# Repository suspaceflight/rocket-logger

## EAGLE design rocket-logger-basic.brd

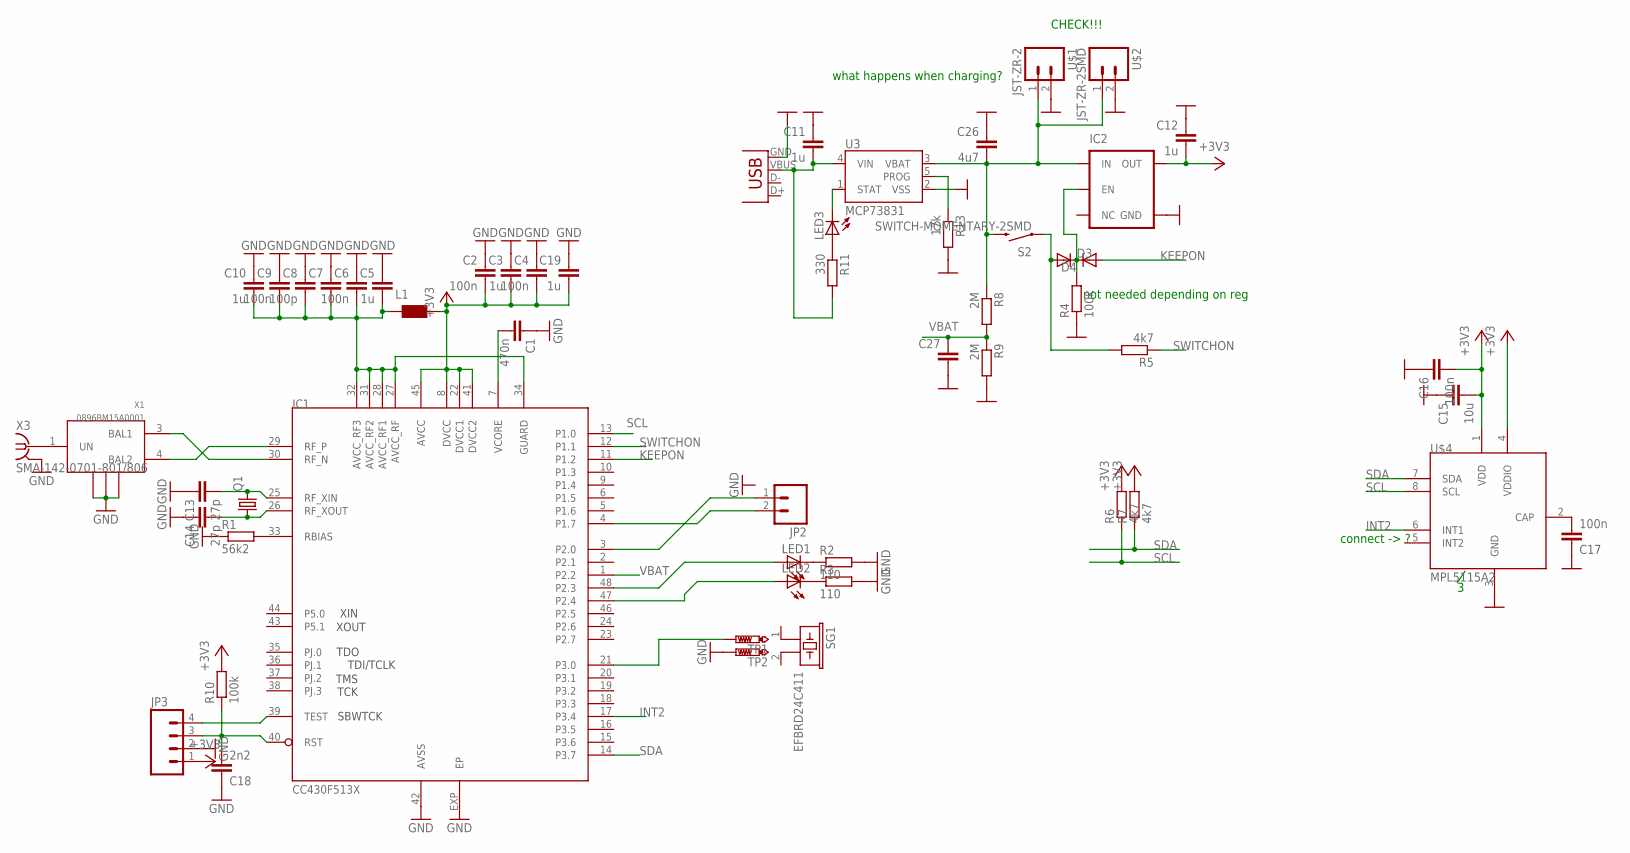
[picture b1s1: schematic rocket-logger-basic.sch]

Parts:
C1: 470n; C0402
C2, C4, C6, C9, C16, C17: 100n; C0402
C3, C5, C10, C11, C12, C19: 1u; C0402
C7, C27: C-EUC0402; C0402
C8: 100p; C0402
C13, C14: 27p; C0402
C15: 10u; C0402
C18: 2n2; C0402
C26: 4u7; C0402
D3, D4: DIODE-SOD523; SOD523
IC1: CC430F513X; QFN48
IC2: V_REG_TPS76433SOT23-5; SOT23-5
JP2: M02PTH; 1X02
JP3: M04PTH; 1X04
L1: WE-MK_0603; 0603
LED1, LED2, LED3: LED0603; LED-0603
Q1: CRYSTAL5X3; CRYSTAL-SMD-5X3
R1: 56k2; R0402
R2, R3: 110; R0402
R4, R10: 100k; R0402
R5, R6, R7: 4k7; R0402
R8, R9: 2M; R0402
R11: 330; R0402
R13: 17k; R0402
S2: SWITCH-MOMENTARY-2SMD; TACTILE_SWITCH_SMD
SG1: EFBRD24C411
TP1, TP2: PTR1B1,27; B1,27
U3: MCP73831; SOT23-5
U$1: JST-ZR-2
U$2: JST-ZR-2SMD; JST-ZR-2-SMD
U$4: MPL5115A2; LGA8
X1: 0896BM15A0001
X2: USB-MICROB
X3: SMA-142-0701-801/806; J502-ND-142-0701-801/806

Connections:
+3V3: C2.2, C3.2, C4.2, C12.2, C15.2, C16.2, C19.2, IC1.8 (DVCC), IC1.22 (DVCC1), IC1.41 (DVCC2), IC1.45 (AVCC), IC2.5 (OUT), JP3.1, L1.2, R6.2, R7.2, R10.2, U$4.1 (VDD), U$4.4 (VDDIO)
AVCC_RF2: C5.2, C6.2, C7.2, C8.2, C9.2, C10.2, IC1.27 (AVCC_RF), IC1.28 (AVCC_RF1), IC1.31 (AVCC_RF2), IC1.32 (AVCC_RF3), IC1.34 (GUARD), L1.1
GND: C1.1, C2.1, C3.1, C4.1, C5.1, C6.1, C7.1, C8.1, C9.1, C10.1, C11.1, C12.1, C13.1, C14.1, C15.1, C16.1, C17.1, C18.1, C19.1, C26.1, C27.2, IC1.42 (AVSS), IC1.EXP (EP), IC2.2 (GND), JP3.2, R1.1, R2.2, R3.2, R4.1, R9.2, R13.2, TP2.TP, U3.2 (VSS), U$1.2, U$2.2, U$4.3 (GND), X1.2 (GND2), X1.5 (GND), X1.6 (GND1), X2.GND, X3.G@1 (GND), X3.G@2 (GND), X3.G@3 (GND), X3.G@4 (GND)
INT2: IC1.17 (P3.4), U$4.6 (INT1)
KEEPON: D4.A, IC1.11 (P1.2)
unnamed: R13.1, U3.5 (PROG)
unnamed: C26.2, IC2.1 (IN), R8.1, S2.3 (2), U3.3 (VBAT), U$1.1, U$2.1
unnamed: IC1.30 (RF_N), X1.3 (BAL1)
unnamed: IC1.29 (RF_P), X1.4 (BAL2)
unnamed: IC1.33 (RBIAS), R1.2
unnamed: C13.2, IC1.25 (RF_XIN), Q1.3 (2)
unnamed: C14.2, IC1.26 (RF_XOUT), Q1.1
unnamed: X1.1 (UN), X3.1
unnamed: LED1.C, R2.1
unnamed: LED2.C, R3.1
unnamed: IC1.3 (P2.0), JP2.1
unnamed: IC1.4 (P1.7), JP2.2
unnamed: C17.2, U$4.2 (CAP)
unnamed: LED3.A, R11.1
unnamed: IC1.48 (P2.3), LED1.A
unnamed: C11.2, R11.2, U3.4 (VIN), X2.VBUS
unnamed: LED3.C, U3.1 (STAT)
unnamed: IC1.39 (TEST), JP3.4
unnamed: D3.A, R5.2, S2.1
unnamed: D3.C, D4.C, IC2.3 (EN), R4.2
unnamed: C18.2, IC1.40 (RST), JP3.3, R10.1
unnamed: IC1.47 (P2.4), LED2.A
unnamed: IC1.21 (P3.0), TP1.TP
SCL: IC1.13 (P1.0), R6.1, U$4.8 (SCL)
SDA: IC1.14 (P3.7), R7.1, U$4.7 (SDA)
SWITCHON: IC1.12 (P1.1), R5.1
VBAT: C27.1, IC1.1 (P2.2), R8.2, R9.1
VCORE: C1.2, IC1.7 (VCORE)

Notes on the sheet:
CHECK!!!
connect -> ?
what happens when charging?
not needed depending on reg

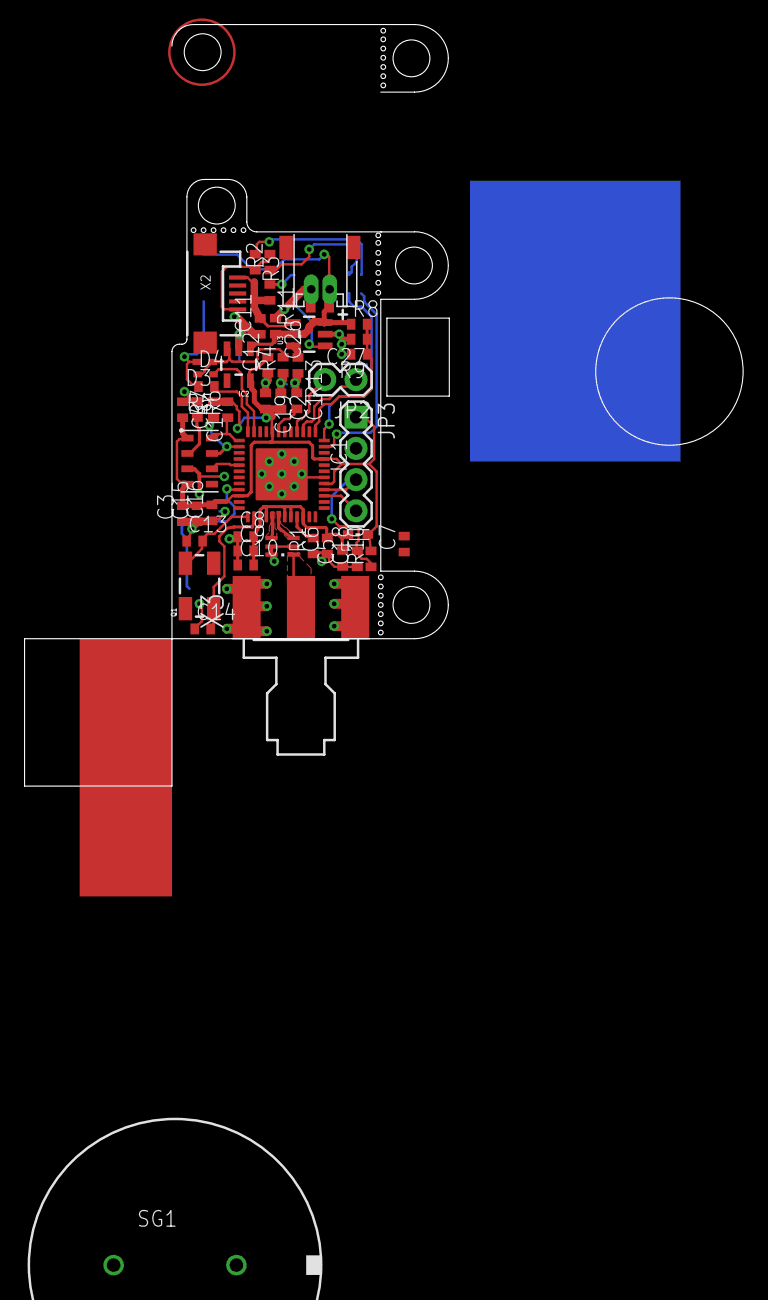
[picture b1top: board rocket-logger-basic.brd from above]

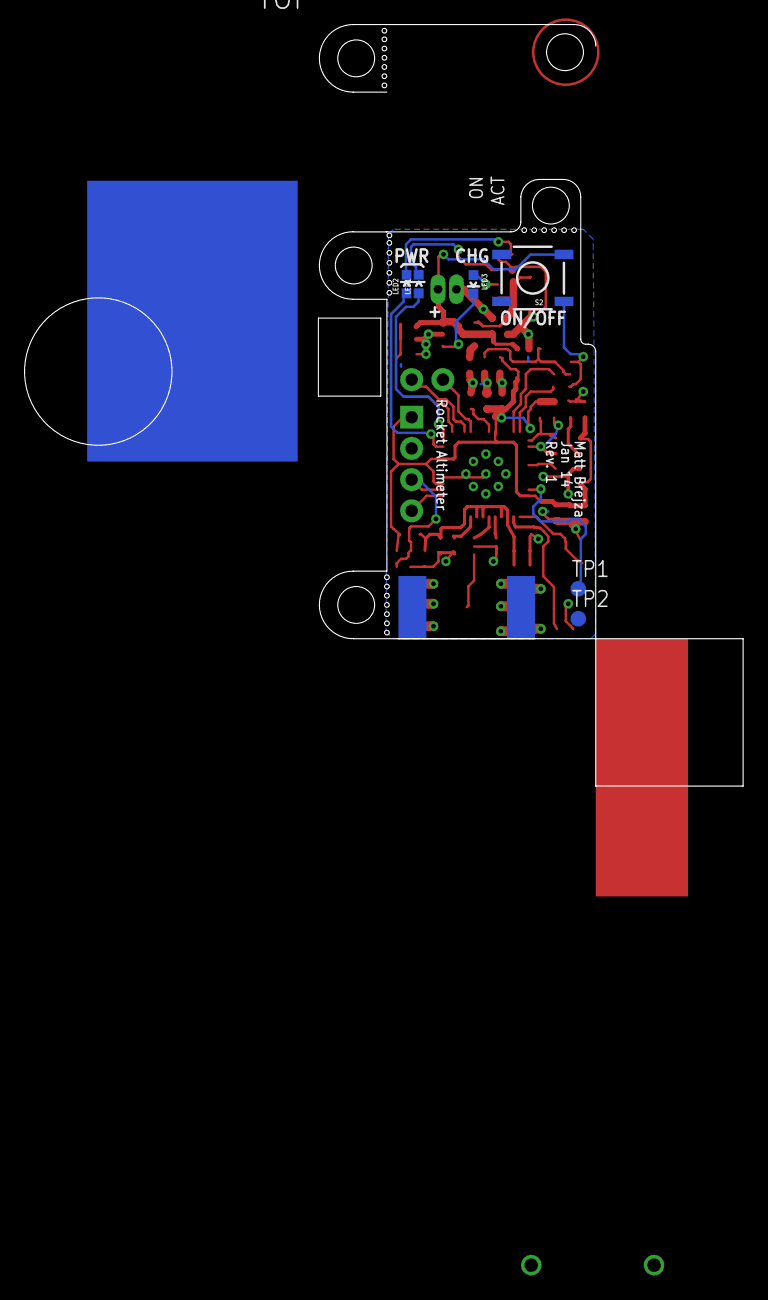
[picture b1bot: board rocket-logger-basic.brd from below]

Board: 2 copper layers, 34.5 x 49.4 mm, 55 parts (6 on the bottom side), 33 nets.

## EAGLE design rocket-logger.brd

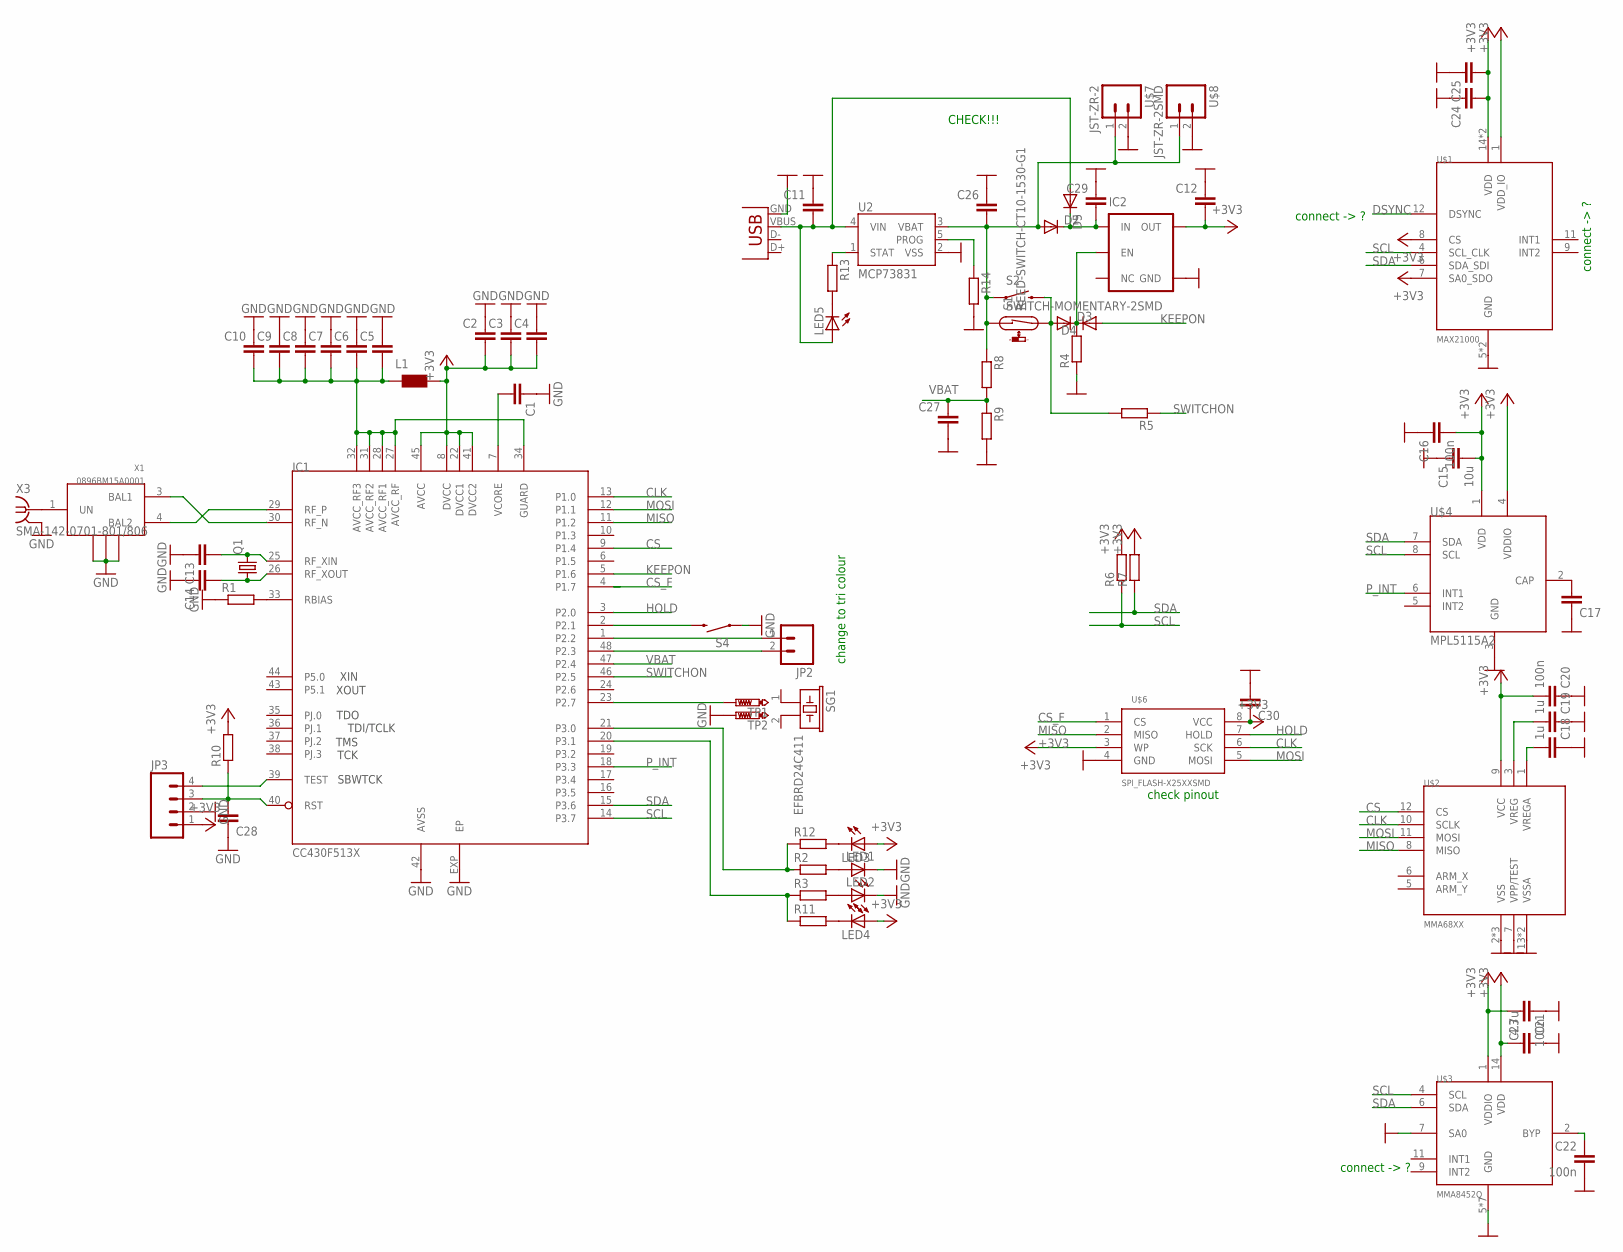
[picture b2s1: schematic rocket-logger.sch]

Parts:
C1, C2, C3, C4, C5, C6, C7, C8, C9, C10, C11, C12, C13, C14, C17, C24, C25, C26, C27, C28, C29, C30: C-EUC0402; C0402
C15: 10u; C0402
C16, C20, C22, C23: 100n; C0402
C18, C19: 1u; C0402
C21: 4.7u; C0402
D2, D3, D4, D5: DIODE-SOD523; SOD523
IC1: CC430F513X; QFN48
IC2: V_REG_TPS76433SOT23-5; SOT23-5
JP2: M02PTH; 1X02
JP3: M04PTH; 1X04
L1: WE-MK_0603; 0603
LED1, LED2, LED3, LED4, LED5: LED0603; LED-0603
Q1: CRYSTAL5X3; CRYSTAL-SMD-5X3
R1, R2, R3, R4, R5, R6, R7, R8, R9, R10, R11, R12, R13, R14: R-EU_R0402; R0402
S1: REED-SWITCH-CT10-1530-G1; CT10-G1
S2, S4: SWITCH-MOMENTARY-2SMD; TACTILE_SWITCH_SMD
SG1: EFBRD24C411
TP1, TP2: PTR1B1,27; B1,27
U2: MCP73831; SOT23-5
U$1: MAX21000; LGA16
U$2: MMA68XX; QFN16-6X6
U$3: MMA8452Q; QFN16-COL
U$4: MPL5115A2; LGA8
U$6: SPI_FLASH-X25XXSMD; SO08
U$7: JST-ZR-2
U$8: JST-ZR-2SMD; JST-ZR-2-SMD
X1: 0896BM15A0001
X2: USB-MICROB
X3: SMA-142-0701-801/806; J502-ND-142-0701-801/806

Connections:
+3V3: C2.2, C3.2, C4.2, C12.2, C15.2, C16.2, C20.2, C21.2, C23.1, C24.2, C25.2, C30.1, IC1.8 (DVCC), IC1.22 (DVCC1), IC1.41 (DVCC2), IC1.45 (AVCC), IC2.5 (OUT), JP3.1, L1.2, LED3.A, LED4.A, R6.2, R7.2, R10.2, U$1.1 (VDD_IO), U$1.7 (SA0_SDO), U$1.8 (CS), U$1.14 (VDD), U$1.15 (VDD), U$2.9 (VCC), U$3.1 (VDDIO), U$3.14 (VDD), U$4.1 (VDD), U$4.4 (VDDIO), U$6.3 (WP), U$6.8 (VCC)
AVCC_RF2: C5.2, C6.2, C7.2, C8.2, C9.2, C10.2, IC1.27 (AVCC_RF), IC1.28 (AVCC_RF1), IC1.31 (AVCC_RF2), IC1.32 (AVCC_RF3), IC1.34 (GUARD), L1.1
CLK: IC1.13 (P1.0), U$2.10 (SCLK), U$6.6 (SCK)
CS: IC1.9 (P1.4), U$2.12 (CS)
CS_F: IC1.4 (P1.7), U$6.1 (CS)
DSYNC: U$1.12 (DSYNC)
GND: C1.1, C2.1, C3.1, C4.1, C5.1, C6.1, C7.1, C8.1, C9.1, C10.1, C11.1, C12.1, C13.1, C14.1, C15.1, C16.1, C17.1, C18.1, C19.1, C20.1, C21.1, C22.2, C23.2, C24.1, C25.1, C26.1, C27.2, C28.1, C29.1, C30.2, IC1.42 (AVSS), IC1.EXP (EP), IC2.2 (GND), JP3.2, LED1.C, LED2.C, R1.1, R4.1, R9.2, R14.2, S4.1, TP2.TP, U2.2 (VSS), U$1.5 (GND), U$1.10 (GND), U$2.2 (VSS), U$2.4 (VSS), U$2.7 (VPP/TEST), U$2.13 (VSSA), U$2.16 (VSSA), U$2.17 (VSS), U$3.5 (GND), U$3.7 (SA0), U$3.8 (GND), U$3.10 (GND), U$3.12 (GND), U$3.13 (GND), U$3.15 (GND), U$3.16 (GND), U$4.3 (GND), U$6.4 (GND), U$7.2, U$8.2, X1.2 (GND2), X1.5 (GND), X1.6 (GND1), X2.GND, X3.G@1 (GND), X3.G@2 (GND), X3.G@3 (GND), X3.G@4 (GND)
HOLD: IC1.3 (P2.0), U$6.7 (HOLD)
KEEPON: D4.A, IC1.5 (P1.6)
MISO: IC1.11 (P1.2), U$2.8 (MISO), U$6.2 (MISO)
MOSI: IC1.12 (P1.1), U$2.11 (MOSI), U$6.5 (MOSI)
unnamed: C11.2, D5.A, LED5.A, U2.4 (VIN), X2.VBUS
unnamed: C26.2, D2.A, R8.1, S1.1, S2.1, U2.3 (VBAT), U$7.1, U$8.1
unnamed: IC1.30 (RF_N), X1.3 (BAL1)
unnamed: IC1.29 (RF_P), X1.4 (BAL2)
unnamed: IC1.33 (RBIAS), R1.2
unnamed: C13.2, IC1.25 (RF_XIN), Q1.3 (2)
unnamed: C14.2, IC1.26 (RF_XOUT), Q1.1
unnamed: X1.1 (UN), X3.1
unnamed: LED1.A, R2.2
unnamed: R13.1, U2.1 (STAT)
unnamed: IC1.1 (P2.2), JP2.1
unnamed: IC1.48 (P2.3), JP2.2
unnamed: C17.2, U$4.2 (CAP)
unnamed: C18.2, U$2.1 (VREGA)
unnamed: C19.2, U$2.3 (VREG)
unnamed: IC1.21 (P3.0), R2.1, R12.1
unnamed: IC1.20 (P3.1), R3.1, R11.1
unnamed: LED5.C, R13.2
unnamed: C22.1, U$3.2 (BYP)
unnamed: LED2.A, R3.2
unnamed: LED4.C, R11.2
unnamed: LED3.C, R12.2
unnamed: IC1.39 (TEST), JP3.4
unnamed: D3.A, R5.2, S1.2, S2.3 (2)
unnamed: D3.C, D4.C, IC2.3 (EN), R4.2
unnamed: C28.2, IC1.40 (RST), JP3.3, R10.1
unnamed: IC1.2 (P2.1), S4.3 (2)
unnamed: IC1.23 (P2.7), TP1.TP
unnamed: C29.2, D2.C, D5.C, IC2.1 (IN)
unnamed: R14.1, U2.5 (PROG)
P_INT: IC1.18 (P3.3), U$4.6 (INT1)
SCL: IC1.14 (P3.7), R6.1, U$1.4 (SCL_CLK), U$3.4 (SCL), U$4.8 (SCL)
SDA: IC1.15 (P3.6), R7.1, U$1.6 (SDA_SDI), U$3.6 (SDA), U$4.7 (SDA)
SWITCHON: IC1.46 (P2.5), R5.1
VBAT: C27.1, IC1.47 (P2.4), R8.2, R9.1
VCORE: C1.2, IC1.7 (VCORE)

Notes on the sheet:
CHECK!!!
connect -> ?
change to tri colour
check pinout

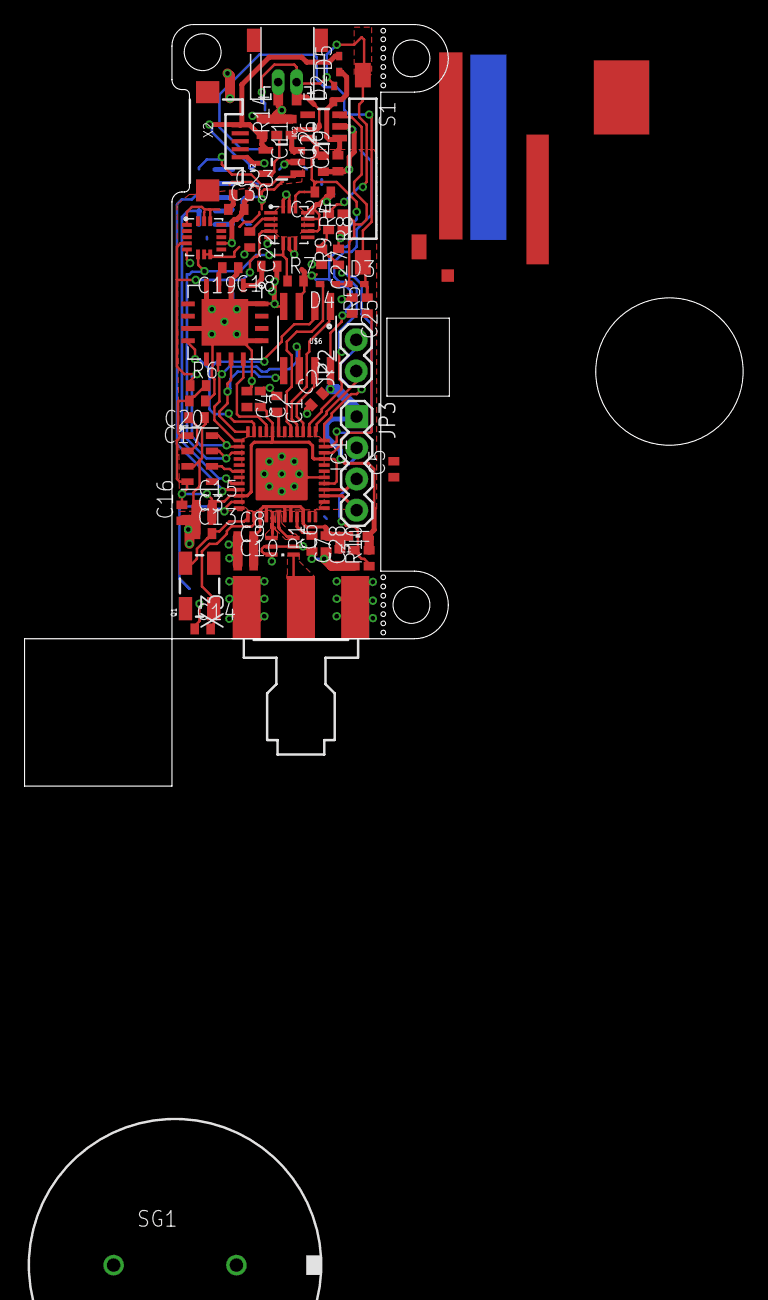
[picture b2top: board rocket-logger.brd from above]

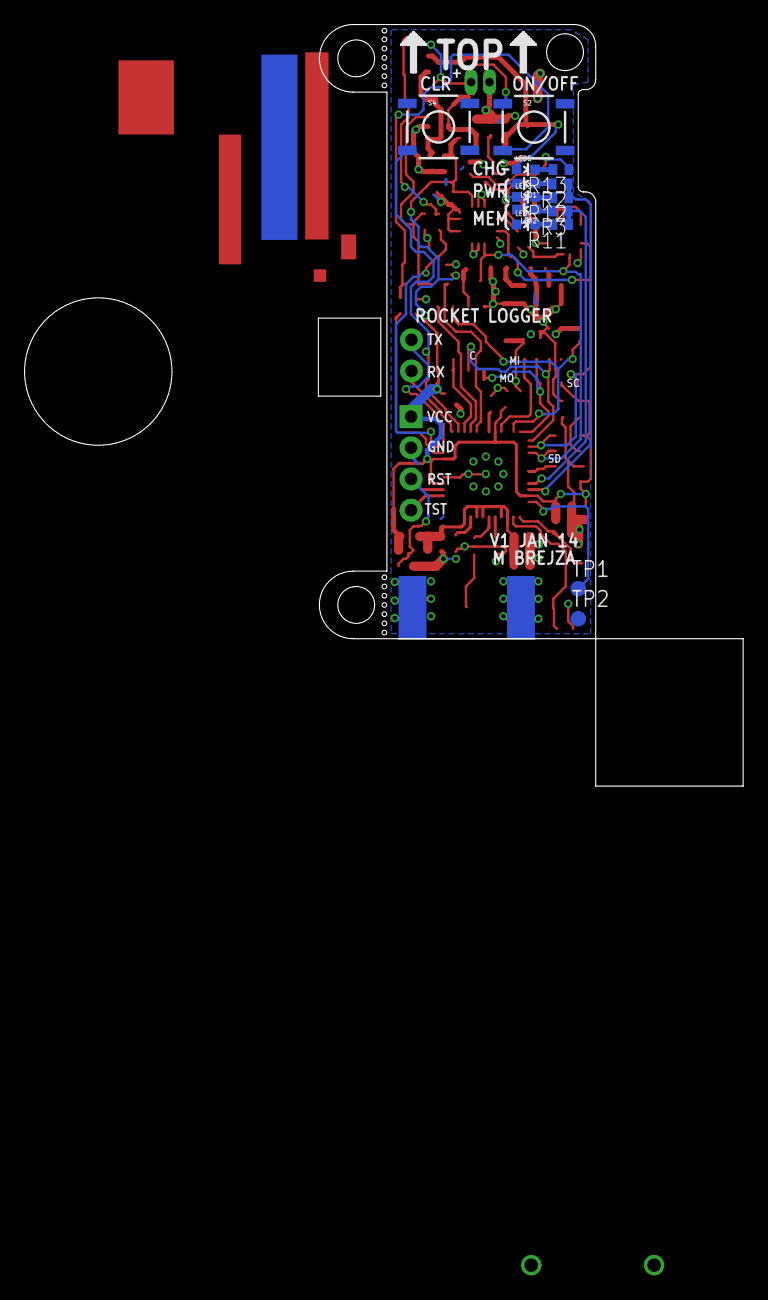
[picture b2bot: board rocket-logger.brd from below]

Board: 2 copper layers, 34.5 x 62.0 mm, 76 parts (14 on the bottom side), 46 nets.

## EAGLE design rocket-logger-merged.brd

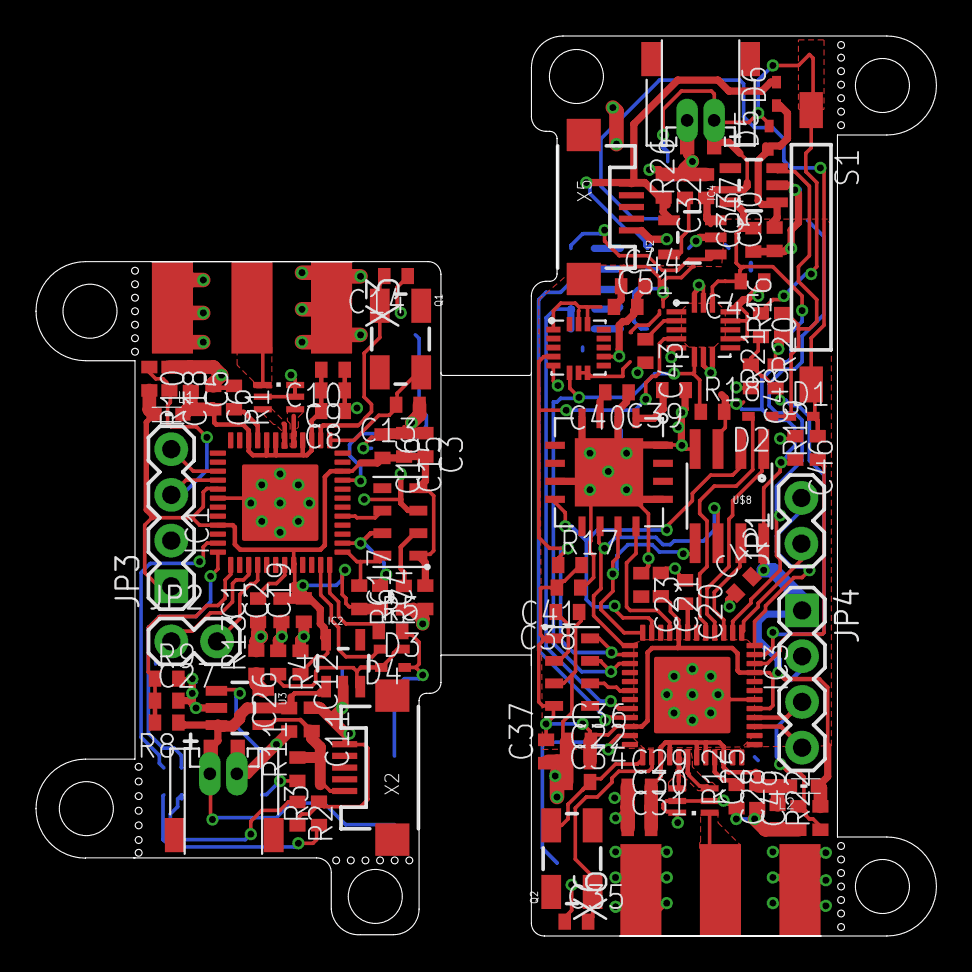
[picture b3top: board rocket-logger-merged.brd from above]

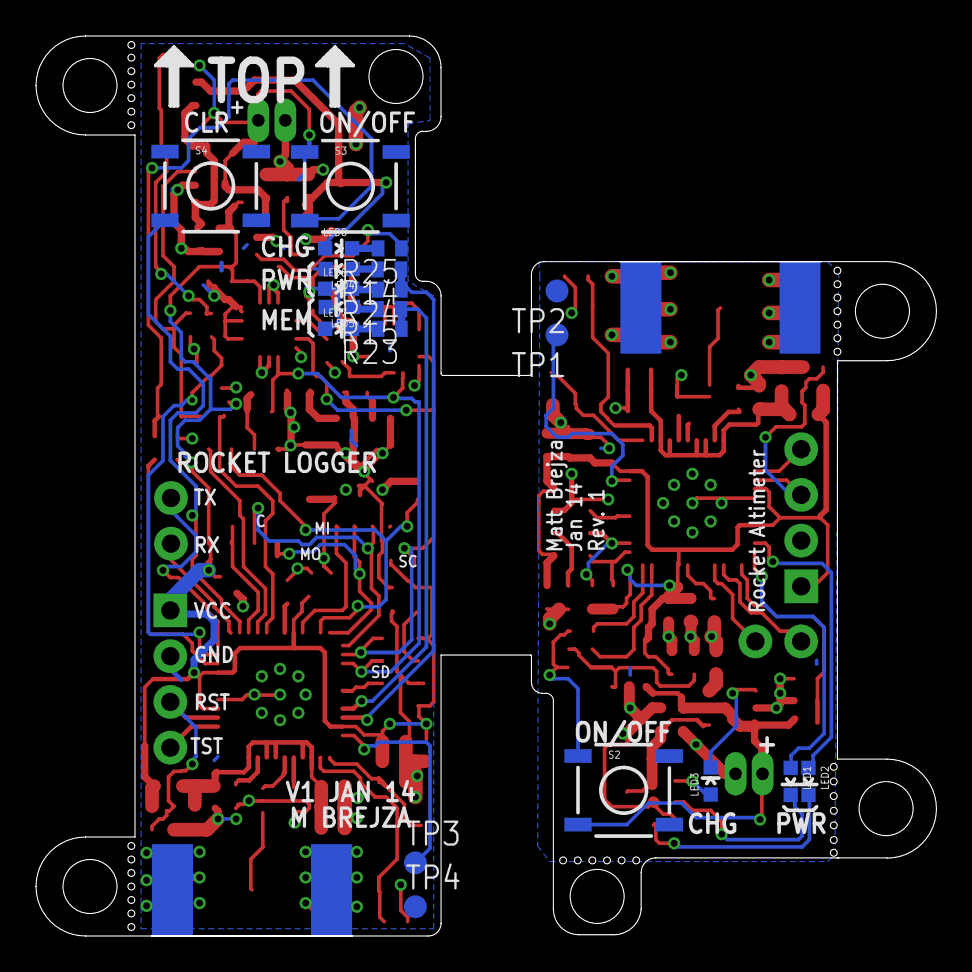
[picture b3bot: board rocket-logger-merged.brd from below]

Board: 2 copper layers, 50.0 x 50.0 mm, 127 parts (20 on the bottom side), 79 nets.

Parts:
C1, C2, C3, C4, C5, C6, C8, C9, C10, C11, C12, C13, C14, C17, C18, C19, C20, C21, C22, C23, C25, C26, C27, C28, C29, C30, C31, C32, C33, C34, C35, C38, C45, C46, C47, C48, C49, C50, C51: C0402
C15, C36: 10u; C0402
C16, C37, C41, C43, C44: 100n; C0402
C39, C40: 1u; C0402
C42: 4.7u; C0402
D1, D2, D3, D4, D5, D6: SOD523
IC1, IC3: CC430F513X; QFN48
IC2, IC4: SOT23-5
JP1, JP2: 1X02
JP3, JP4: 1X04
L1, L2: 0603
LED1, LED2, LED3, LED4, LED5, LED6, LED7, LED8: LED-0603
Q1, Q2: CRYSTAL-SMD-5X3
R1, R2, R3, R4, R5, R6, R7, R8, R9, R10, R11, R12, R13, R14, R15, R16, R17, R18, R19, R20, R21, R22, R23, R24, R25, R26: R0402
S1: REED-SWITCH-CT10-1530-G1; CT10-G1
S2, S3, S4: SWITCH-MOMENTARY-2SMD; TACTILE_SWITCH_SMD
TP1, TP2, TP3, TP4: PTR1B1,27; B1,27
U2, U3: MCP73831; SOT23-5
U$1, U$9: JST-ZR-2
U$2, U$10: JST-ZR-2SMD; JST-ZR-2-SMD
U$3: MAX21000; LGA16
U$4, U$7: MPL5115A2; LGA8
U$5: MMA68XX; QFN16-6X6
U$6: MMA8452Q; QFN16-COL
U$8: SPI_FLASH-X25XXSMD; SO08
X1, X4: 0896BM15A0001
X2, X5: USB-MICROB
X3, X6: SMA-142-0701-801/806; J502-ND-142-0701-801/806

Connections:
+3V1: C21.2, C22.2, C23.2, C33.2, C36.2, C37.2, C41.2, C42.2, C44.1, C45.2, C46.2, C51.1, IC3.8, IC3.22, IC3.41, IC3.45, IC4.5, JP4.1, L2.2, LED6.A, LED7.A, R17.2, R18.2, R22.2, U$3.1, U$3.7, U$3.8, U$3.14, U$3.15, U$5.9, U$6.1, U$6.14, U$7.1, U$7.4, U$8.3, U$8.8
+3V3: C2.2, C3.2, C4.2, C12.2, C15.2, C16.2, C19.2, IC1.8, IC1.22, IC1.41, IC1.45, IC2.5, JP3.1, L1.2, R6.2, R7.2, R10.2, U$4.1, U$4.4
AVCC_RF1: C25.2, C28.2, C29.2, C30.2, C31.2, IC3.27, IC3.28, IC3.31, IC3.32, IC3.34, L2.1
AVCC_RF2: C5.2, C6.2, C8.2, C9.2, C10.2, IC1.27, IC1.28, IC1.31, IC1.32, IC1.34, L1.1
CLK: IC3.13, U$5.10, U$8.6
CS: IC3.9, U$5.12
CS_F: IC3.4, U$8.1
GND: C1.1, C2.1, C3.1, C4.1, C5.1, C6.1, C8.1, C9.1, C10.1, C11.1, C12.1, C13.1, C14.1, C15.1, C16.1, C17.1, C18.1, C19.1, C26.1, C27.2, IC1.42, IC1.EXP, IC2.2, JP3.2, R1.1, R2.2, R3.2, R4.1, R9.2, R13.2, TP2.TP, U3.2, U$1.2, U$2.2, U$4.3, X1.2, X1.5, X1.6, X2.GND, X3.G@1, X3.G@2, X3.G@3, X3.G@4
GND1: C20.1, C21.1, C22.1, C23.1, C25.1, C28.1, C29.1, C30.1, C31.1, C32.1, C33.1, C34.1, C35.1, C36.1, C37.1, C38.1, C39.1, C40.1, C41.1, C42.1, C43.2, C44.2, C45.1, C46.1, C47.1, C48.2, C49.1, C50.1, C51.2, IC3.42, IC3.EXP, IC4.2, JP4.2, LED4.C, LED5.C, R12.1, R16.1, R21.2, R26.2, S4.1, TP4.TP, U2.2, U$3.5, U$3.10, U$5.2, U$5.4, U$5.7, U$5.13, U$5.16, U$5.17, U$6.5, U$6.7, U$6.8, U$6.10, U$6.12, U$6.13, U$6.15, U$6.16, U$7.3, U$8.4, U$9.2, U$10.2, X4.2, X4.5, X4.6, X5.GND, X6.G@1, X6.G@2, X6.G@3, X6.G@4
HOLD: IC3.3, U$8.7
INT2: IC1.17, U$4.6
KEEPON: D4.A, IC1.11
KEEPON1: D2.A, IC3.5
MISO: IC3.11, U$5.8, U$8.2
MOSI: IC3.12, U$5.11, U$8.5
unnamed: R13.1, U3.5
unnamed: C26.2, IC2.1, R8.1, S2.3, U3.3, U$1.1, U$2.1
unnamed: IC1.30, X1.3
unnamed: IC1.29, X1.4
unnamed: IC1.33, R1.2
unnamed: C13.2, IC1.25, Q1.3
unnamed: C14.2, IC1.26, Q1.1
unnamed: X1.1, X3.1
unnamed: LED1.C, R2.1
unnamed: LED2.C, R3.1
unnamed: IC1.3, JP2.1
unnamed: IC1.4, JP2.2
unnamed: C17.2, U$4.2
unnamed: C32.2, D6.A, LED8.A, U2.4, X5.VBUS
unnamed: LED3.A, R11.1
unnamed: IC1.48, LED1.A
unnamed: C47.2, D5.A, R20.1, S1.1, S3.1, U2.3, U$9.1, U$10.1
unnamed: C11.2, R11.2, U3.4, X2.VBUS
unnamed: LED3.C, U3.1
unnamed: IC3.30, X4.3
unnamed: IC3.33, R12.2
unnamed: C34.2, IC3.25, Q2.3
unnamed: IC1.39, JP3.4
unnamed: D3.A, R5.2, S2.1
unnamed: D3.C, D4.C, IC2.3, R4.2
unnamed: C18.2, IC1.40, JP3.3, R10.1
unnamed: C35.2, IC3.26, Q2.1
unnamed: IC1.47, LED2.A
unnamed: IC1.21, TP1.TP
unnamed: X4.1, X6.1
unnamed: IC3.29, X4.4
unnamed: C38.2, U$7.2
unnamed: C39.2, U$5.1
unnamed: C40.2, U$5.3
unnamed: C43.1, U$6.2
unnamed: IC3.21, R14.1, R24.1
unnamed: IC3.20, R15.1, R23.1
unnamed: IC3.1, JP1.1
unnamed: IC3.48, JP1.2
unnamed: D1.A, R19.2, S1.2, S3.3
unnamed: D1.C, D2.C, IC4.3, R16.2
unnamed: IC3.39, JP4.4
unnamed: C49.2, IC3.40, JP4.3, R22.1
unnamed: IC3.2, S4.3
unnamed: IC3.23, TP3.TP
unnamed: LED5.A, R15.2
unnamed: LED7.C, R23.2
unnamed: LED4.A, R14.2
unnamed: LED6.C, R24.2
unnamed: LED8.C, R25.2
unnamed: C50.2, D5.C, D6.C, IC4.1
unnamed: R25.1, U2.1
unnamed: R26.1, U2.5
P_INT: IC3.18, U$7.6
SCL: IC1.13, R6.1, U$4.8
SCL1: IC3.14, R17.1, U$3.4, U$6.4, U$7.8
SDA: IC1.14, R7.1, U$4.7
SDA1: IC3.15, R18.1, U$3.6, U$6.6, U$7.7
SWITCHON: IC1.12, R5.1
SWITCHON1: IC3.46, R19.1
VBAT: C27.1, IC1.1, R8.2, R9.1
VBAT1: C48.1, IC3.47, R20.2, R21.1
VCORE: C1.2, IC1.7
VCORE1: C20.2, IC3.7

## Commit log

2013-10-13 initial commit of eagle files
2013-10-13 now with added flash
2013-10-14 added sounder layout
2013-10-14 moving stuff around a bit
2013-10-14 routing
2013-10-14 wired sounder
2013-10-15 added mini logger
2013-10-17 some routing - changed to smaller flash
2013-10-18 adding more leds
2013-10-20 removed accel from simple verison, done some routing on main one
2013-10-20 added charging led
2013-10-24 done some routing
2013-10-26 added diodes on power path
2013-10-27 switched to smaller jst connector and done routing
2013-10-28 some more routing
2013-11-02 some routing done, changed lipo charger
2013-11-03 moved leds and done silk layer
2013-11-18 fixing some drc
2013-12-17 minor changes
2013-12-28 basic logger done
2013-12-31 finishing off, almost done
2014-01-06 minor change
2014-01-07 added merged board
2014-01-08 sent off
2014-04-13 initial code commit
2014-04-15 code mostly done but i2c seems broken
2014-04-16 changes sample rates
2014-04-18 min/max tx done, needs testing
2014-05-04 updating ignore
2014-05-04 beginning to get packet radio working
2014-05-04 cc430 to cc1101 working
2014-08-03 should have been done a while agp
2014-09-05 adding battery voltage reporting
2014-10-07 getting power management stuff done
2014-10-09 power mgnt done
2014-10-12 ui update
2014-10-14 ui almost done
2014-10-15 status bar done
2015-01-30 added part values
2015-01-30 adding stencil
2015-02-17 updating component values
2015-02-23 changing value

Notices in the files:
parts and their libraries:
wuerth-elektronik: Copyright: Würth Elektronik eiSos
SparkFun-PowerIC: Licensing: CC v3.0 Share-Alike You are welcome to use this library for commercial purposes.
